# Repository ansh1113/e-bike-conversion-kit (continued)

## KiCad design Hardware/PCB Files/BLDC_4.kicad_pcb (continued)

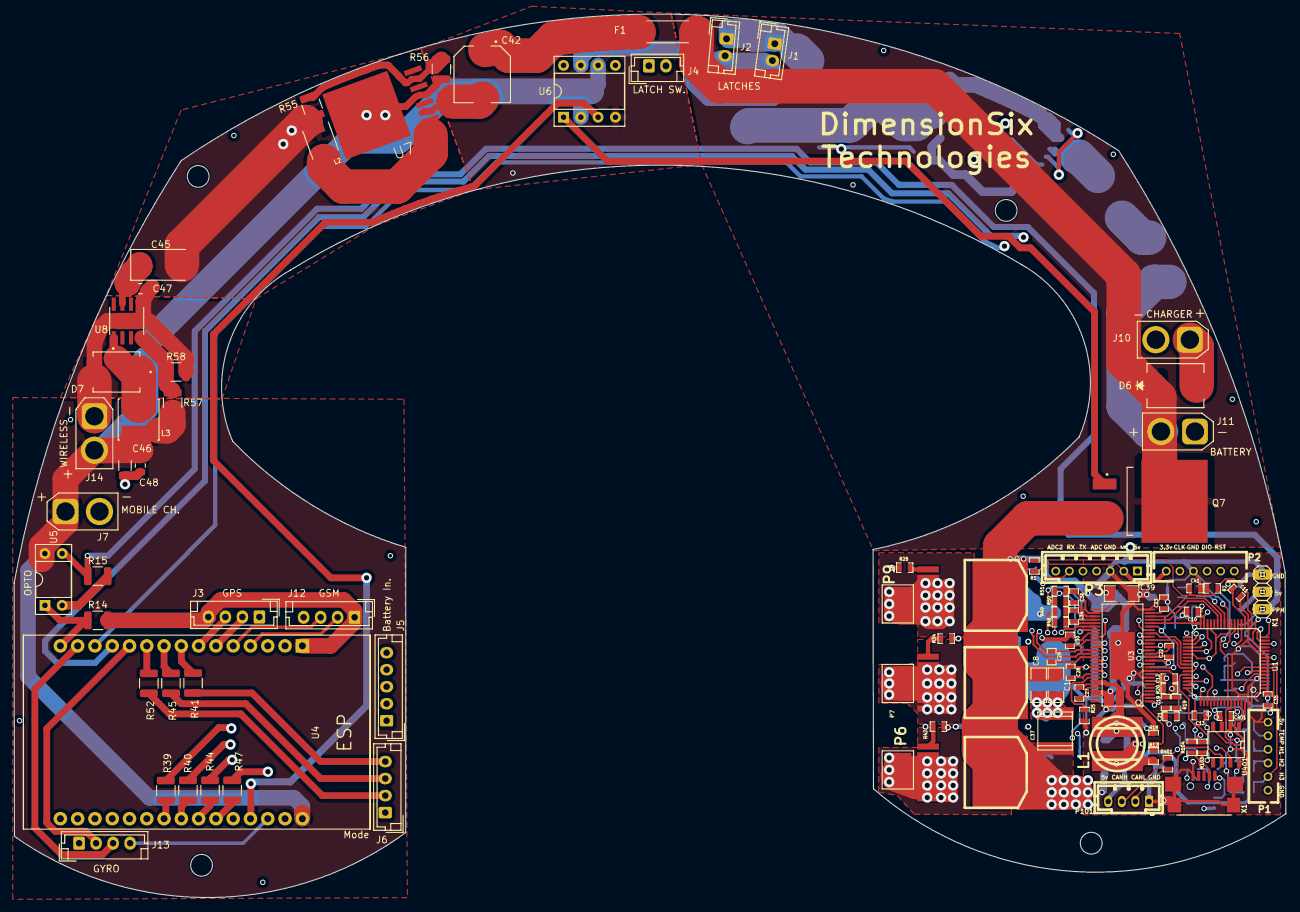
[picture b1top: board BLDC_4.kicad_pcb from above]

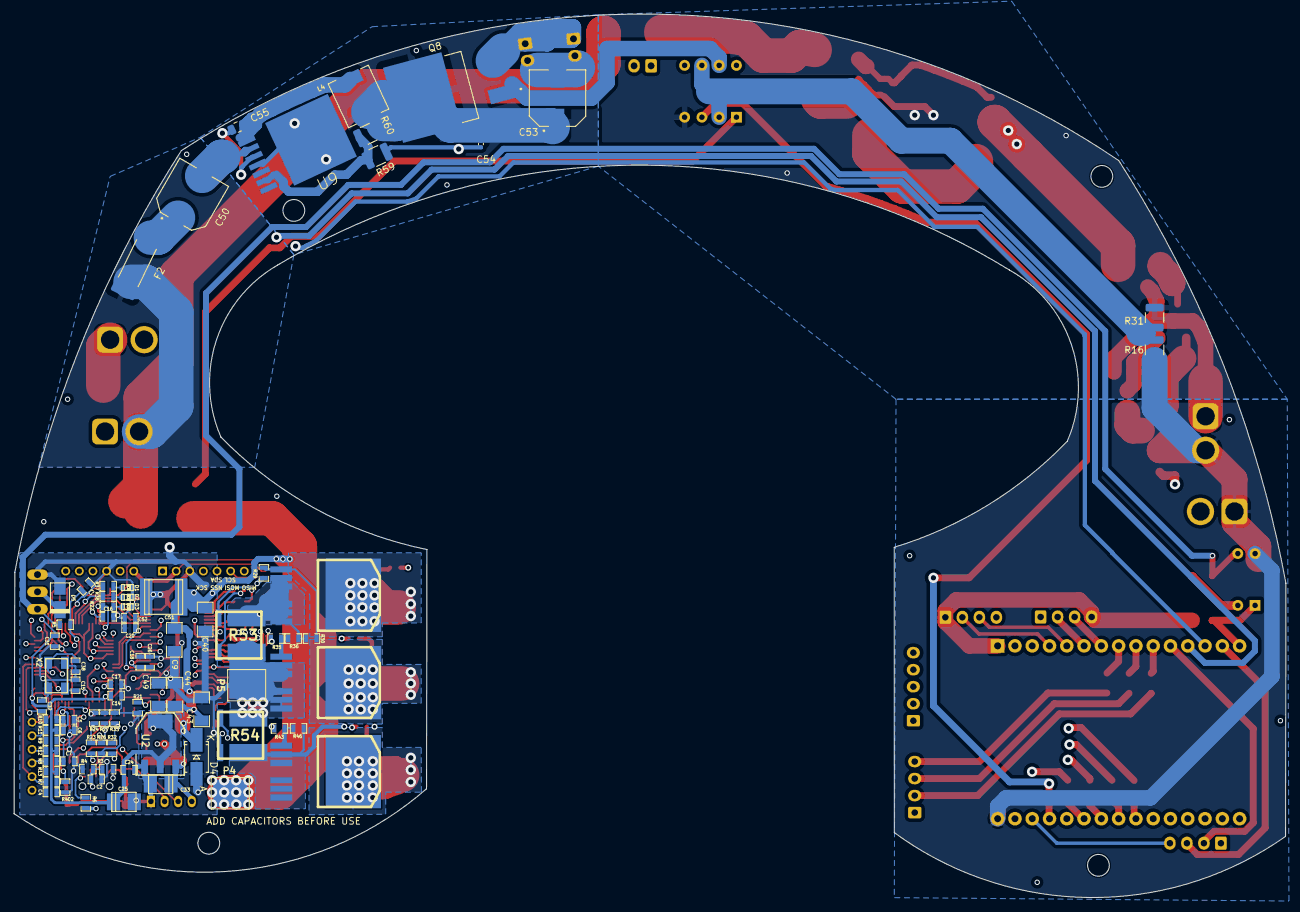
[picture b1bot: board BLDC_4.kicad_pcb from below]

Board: 4 copper layers, 186.9 x 129.8 mm, 178 parts (80 on the bottom side), 143 nets.

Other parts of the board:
H3, H3#2, H3#3: MountingHole; MountingHole_3.2mm_M3

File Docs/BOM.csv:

ld,Designator,Footprint,Quantity,Designation
1,C37,c_2220,1,"15u,100V"
2,K1,pinhead-1X03,1,SERVO
3,P1,MICRO_JST_6,1,HALL/Encoder
4,P2,MICRO_JST_6,1,SWD
5,P6,1PAD_4x5mm,1,MOTOR1
6,P9,1PAD_4x5mm,1,MOTOR3
7,"Q1,Q3,Q5,Q6,Q2,Q4",D2PAK-7-GDS,6,IRFS7530
8,U1,lqfp64_pad_mod,1,STM32F40X_LQFP64
9,U3,TSSOP-56-PP,1,DRV8302
10,P101,b4b-ph-kl,1,CANBUS
11,P7,1PAD_4x5mm,1,MOTOR2
12,"C1,C8,C39,C9,C40,C43,C44,C49",SMD-1206,8,"10u,50V"
13,"C10,C11,C12,C13,C23,C35,C41,C401,C14,C16,C17,C18,C20,C24,C31,C52,C26",SMD-0603_c,17,2.2u
14,C19,SMD-0603_c,1,120p
15,C21,SMD-0603_c,1,6.8n
16,C22,SMD-0603_c,1,22n
17,"C27,C2,C3,C32",SMD-0603_c,4,100n
18,"C28,C29,C30",SMD-0603_c,3,220n
19,"C34,C36",SMD-0603_c,2,2.2n
20,R1,SMD-0603_r,1,NTC 10k
21,"R2,R20,R7,R8,R9,R10,R402",SMD-0603_r,7,10k
22,R17,SMD-0603_r,1,18k
23,R18,SMD-0603_r,1,3k3
24,R19,SMD-0603_r,1,15k
25,R25,SMD-0603_r,1,1M
26,"R28,R34,R42,R29,R35,R43",SMD-0603_r,6,4R7
27,"R48,R49,R50,R51,R37,R38",SMD-0603_r,6,100R
28,"R103,R104",SMD-0603_r,2,22R
29,R401,SMD-0603_r,1,NI
30,U401,SOIC-8-W,1,SN65HVD232
31,X1,USB-UX60R-MB-5ST,1,MINI-USB-SHIELD-32005-201
32,P3,b7b-ph-kl,1,PWR_COMM
33,L1,inductor_smd_8x5mm,1,22u
34,"F1,F2",Fuse_Schurter_UMT250,2,3403.0176.24
35,D6,B560C-13-F,1,B560C-13-F
36,R58,R_1210_3225Metric,1,15k
37,"C48,C47,C58",C_1210_3225Metric,3,CL32A226MOJNNNE
38,U6,DIP-8_W7.62mm_Socket,1,LM358P
39,C57,CAP_A765EB127M1ALAE018_KEM,1,A765EB127M1ALAE018
40,"R41,R45,R52,R44,R39,R47,R40",R_1210_3225Metric,7,2k
41,J8,AMASS_XT30U-F_1x02_P5.0mm_Vertical,1,2-1445098-2
42,"C56,C63,C55",C_0805_2012Metric,3,KAM21BR71H104JT
43,"C46,C45",C_1206_3216Metric,2,CL31A226KAHNNNF
44,"U7,U9",LM22678TJ-ADJNOPB,2,LM22678TJ-ADJ/NOPB
45,R61,R_1210_3225Metric,1,25.5k
46,"J14,J1,J2,J4",JST_EH_B2B-EH-A_1x02_P2.50mm_Vertical,4,XT30PW-M
47,"J6,J13,J12,J3",JST_EH_B4B-EH-A_1x04_P2.50mm_Vertical,4,43650-0402
48,R55,R_1210_3225Metric,1,18.2k
49,U4,MODULE_ESP32_DEVKIT_V1,1,ESP32-DEVKIT-V1
50,"C60,C59",C_0402_1005Metric,2,AC0402KRX7R7BB104
51,U10,TPS25221DRVR,1,TPS25221DRVR
52,"C42,C50,C53",CAP_EEE1HA101UAP,3,EEE1HA101UAP
53,L3,IND_BWVS00808040_PUL,1,BWVS008080403R3M00
54,J11,AMASS_XT30U-F_1x02_P5.0mm_Vertical,1,XT30PW-M
55,U8,AOZ6605PI,1,AOZ6605PI-1
56,R14,R_1210_3225Metric,1,1k
57,C61,C_0805_2012Metric,1,TCC0805X7R222K101DT
58,R15,R_1210_3225Metric,1,1k
59,"C65,C64",C_0805_2012Metric,2,0805X226M160NT
60,U5,DIP-4_W7.62mm_Socket,1,Optoisolator1
61,L2,IND_AMDLA4020S-220MT,1,AMDLA4020S-220MT
62,R63,R_1210_3225Metric,1,47k
63,J7,JST_EH_B2B-EH-A_1x02_P2.50mm_Vertical,1,2-1445098-2
64,R57,R_1210_3225Metric,1,110k
65,J5,JST_EH_B5B-EH-A_1x05_P2.50mm_Vertical,1,171971-0005
66,Q7,VREG_L7805ACD2T,1,STB75NF75T4
67,R62,R_0402_1005Metric,1,5
68,C62,C_0603_1608Metric,1,MC0603X105M160CT
69,"R56,R59",R_1210_3225Metric,2,2.2k
70,"C25,C33",c_tant_B,2,100u
71,C51,c_2220,1,"15u, 100v"
72,D1,LED-0603,1,GREEN
73,D2,LED-0603,1,RED
74,D3,LED-0603,1,LED
75,P4,1PAD_4x5mm,1,IN+
76,P5,1PAD_4x5mm,1,IN-
77,"R53,R54",WSLP2726,2,SHUNT
78,X2,Crystal_5x3mm,1,8MHz 10ppm
79,D5,do214ac,1,TVS 5V
80,"C4,C5,C6,C7",SMD-0603_c,4,4n7
81,"C15,C38",SMD-0603_c,2,15p
82,"R3,R23,R26,R30,R32,R36,R46",SMD-0603_r,7,39k
83,"R4,R5,R11,R12,R13,R22,R24,R27,R33",SMD-0603_r,9,2k2
84,R6,SMD-0603_r,1,0R
85,R21,SMD-0603_r,1,220k
86,U2,SOT-223,1,TC2117
87,D4,SMA_Handsoldering,1,DIODESCH
88,"R16,R31",R_1210_3225Metric,2,2k
89,C54,C_0402_1005Metric,1,MAASL105CD7105MFCA01
90,Q8,TRANS_IRF3205S,1,IRF5305STRLPBF
91,L4,IND_SPM6530T-6R8M-HZ,1,SPM6530T-6R8M
92,R60,R_1210_3225Metric,1,39k

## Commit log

2025-02-21 Initial commit with PCB, firmware, and documentation
2025-02-21 Updated firmware / Fixed bug / Added new feature
2025-02-26 Updated hardware / Fixed bug / Added new feature
2025-02-26 Updated docs / Fixed bug / Added new feature
2025-04-30 Updated schematic
